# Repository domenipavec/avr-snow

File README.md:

# avr-snow

https://domen.ipavec.net/en/snow-jaslice/

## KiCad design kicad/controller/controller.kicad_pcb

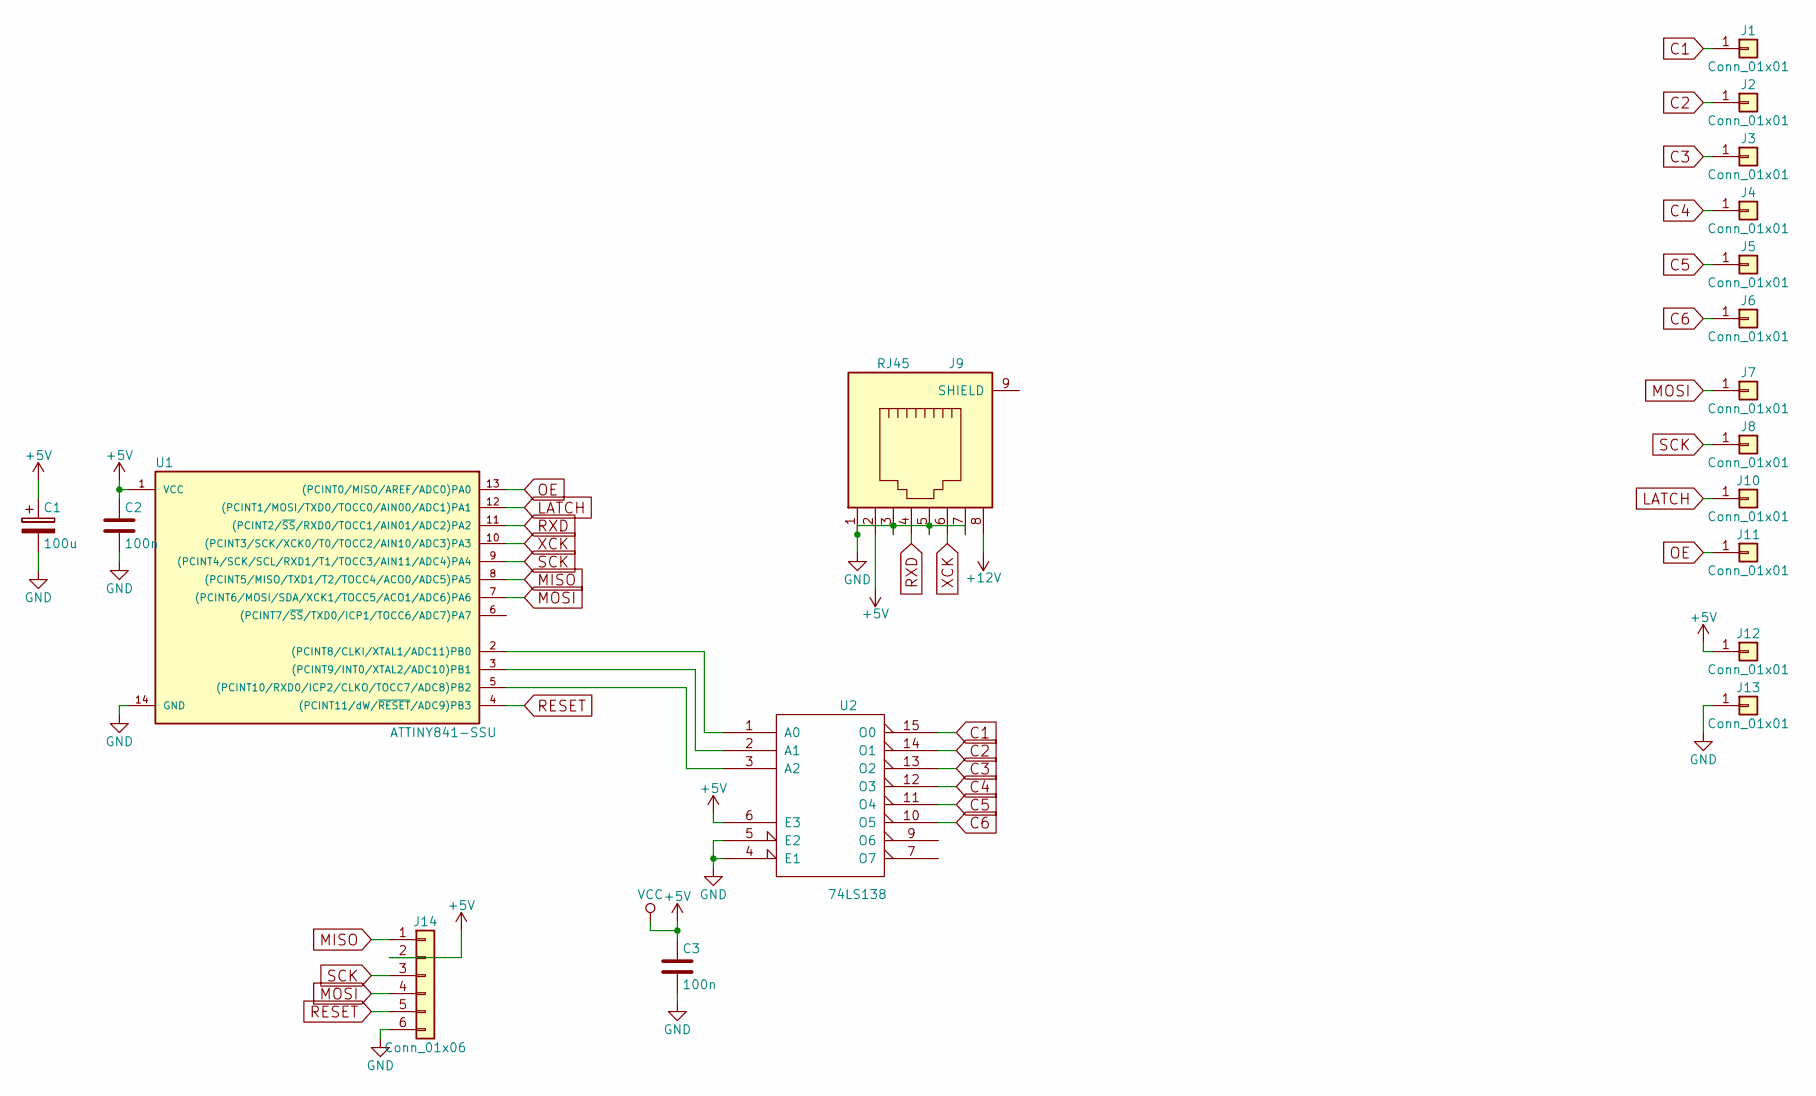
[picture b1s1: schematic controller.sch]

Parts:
C1: 100u; CP_Radial_D6.3mm_P2.50mm
C2, C3: 100n; C_0603_HandSoldering
J1, J2, J3, J4, J5, J6, J7, J8, J10, J11, J12, J13: Conn_01x01; Measurement_Point_Square-SMD-Pad_Big
J9: RJ45
J14: Conn_01x06; Pin_Header_Straight_2x03_Pitch2.54mm
U1: ATTINY841-SSU; SOIC-14_3.9x8.7mm_Pitch1.27mm
U2: 74LS138; SOIC-16W_5.3x10.2mm_Pitch1.27mm

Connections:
+5V: C1.1, C2.1, C3.1, J9.2, J12.1, J14.2, U1.1 (VCC), U2.6 (E3), U2.16 (VCC)
+12V: J9.8
C1: J1.1, U2.15 (O0)
C2: J2.1, U2.14 (O1)
C3: J3.1, U2.13 (O2)
C4: J4.1, U2.12 (O3)
C5: J5.1, U2.11 (O4)
C6: J6.1, U2.10 (O5)
GND: C1.2, C2.2, C3.2, J9.1, J9.3, J9.5, J9.7, J13.1, J14.6, U1.14 (GND), U2.4 (E1), U2.5 (E2), U2.8 (GND)
LATCH: J10.1, U1.12 ((PCINT1/MOSI/TXD0/TOCC0/AIN00/ADC1)PA1)
MISO: J14.1, U1.8 ((PCINT5/MISO/TXD1/T2/TOCC4/ACO0/ADC5)PA5)
MOSI: J7.1, J14.4, U1.7 ((PCINT6/MOSI/SDA/XCK1/TOCC5/ACO1/ADC6)P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)
unnamed: U1.2 ((PCINT8/CLKI/XTAL1/ADC11)PB0), U2.1 (A0)
unnamed: U1.3 ((PCINT9/INT0/XTAL2/ADC10)PB1), U2.2 (A1)
unnamed: U1.5 ((PCINT10/RXD0/ICP2/CLKO/TOCC7/ADC8)PB2), U2.3 (A2)
OE: J11.1, U1.13 ((PCINT0/MISO/AREF/ADC0)PA0)
RESET: J14.5, U1.4 ((PCINT11/dW/~RESET~/ADC9)PB3)
RXD: J9.4, U1.11 ((PCINT2/~SS~/RXD0/TOCC1/AIN01/ADC2)PA2)
SCK: J8.1, J14.3, U1.9 ((PCINT4/SCK/SCL/RXD1/T1/TOCC3/AIN11/ADC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)
XCK: J9.6, U1.10 ((PCINT3/SCK/XCK0/T0/TOCC2/AIN10/ADC3)PA3)

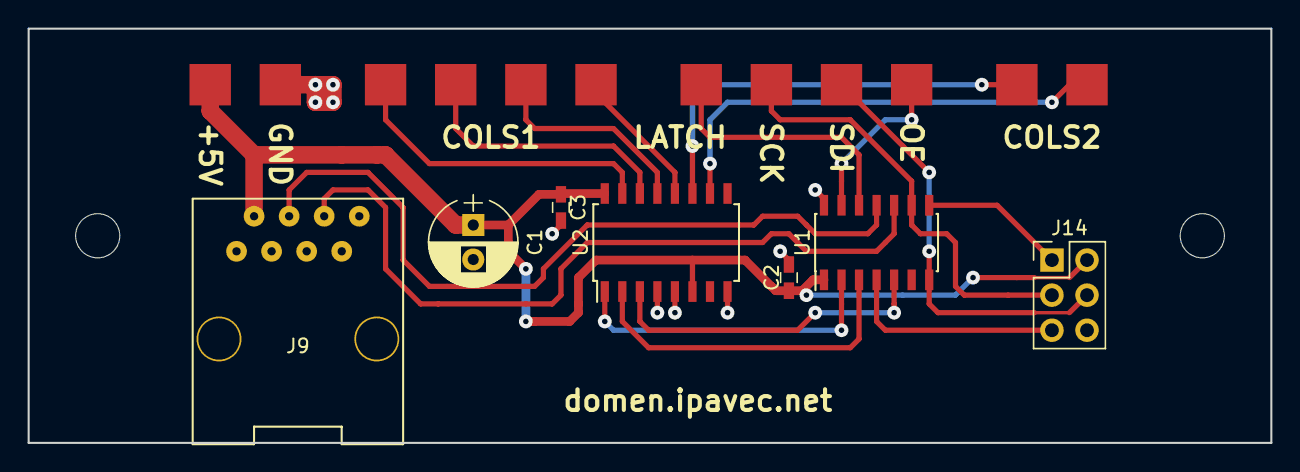
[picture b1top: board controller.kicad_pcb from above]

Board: 2 copper layers, 90.0 x 30.0 mm, 19 parts (0 on the bottom side), 19 nets.

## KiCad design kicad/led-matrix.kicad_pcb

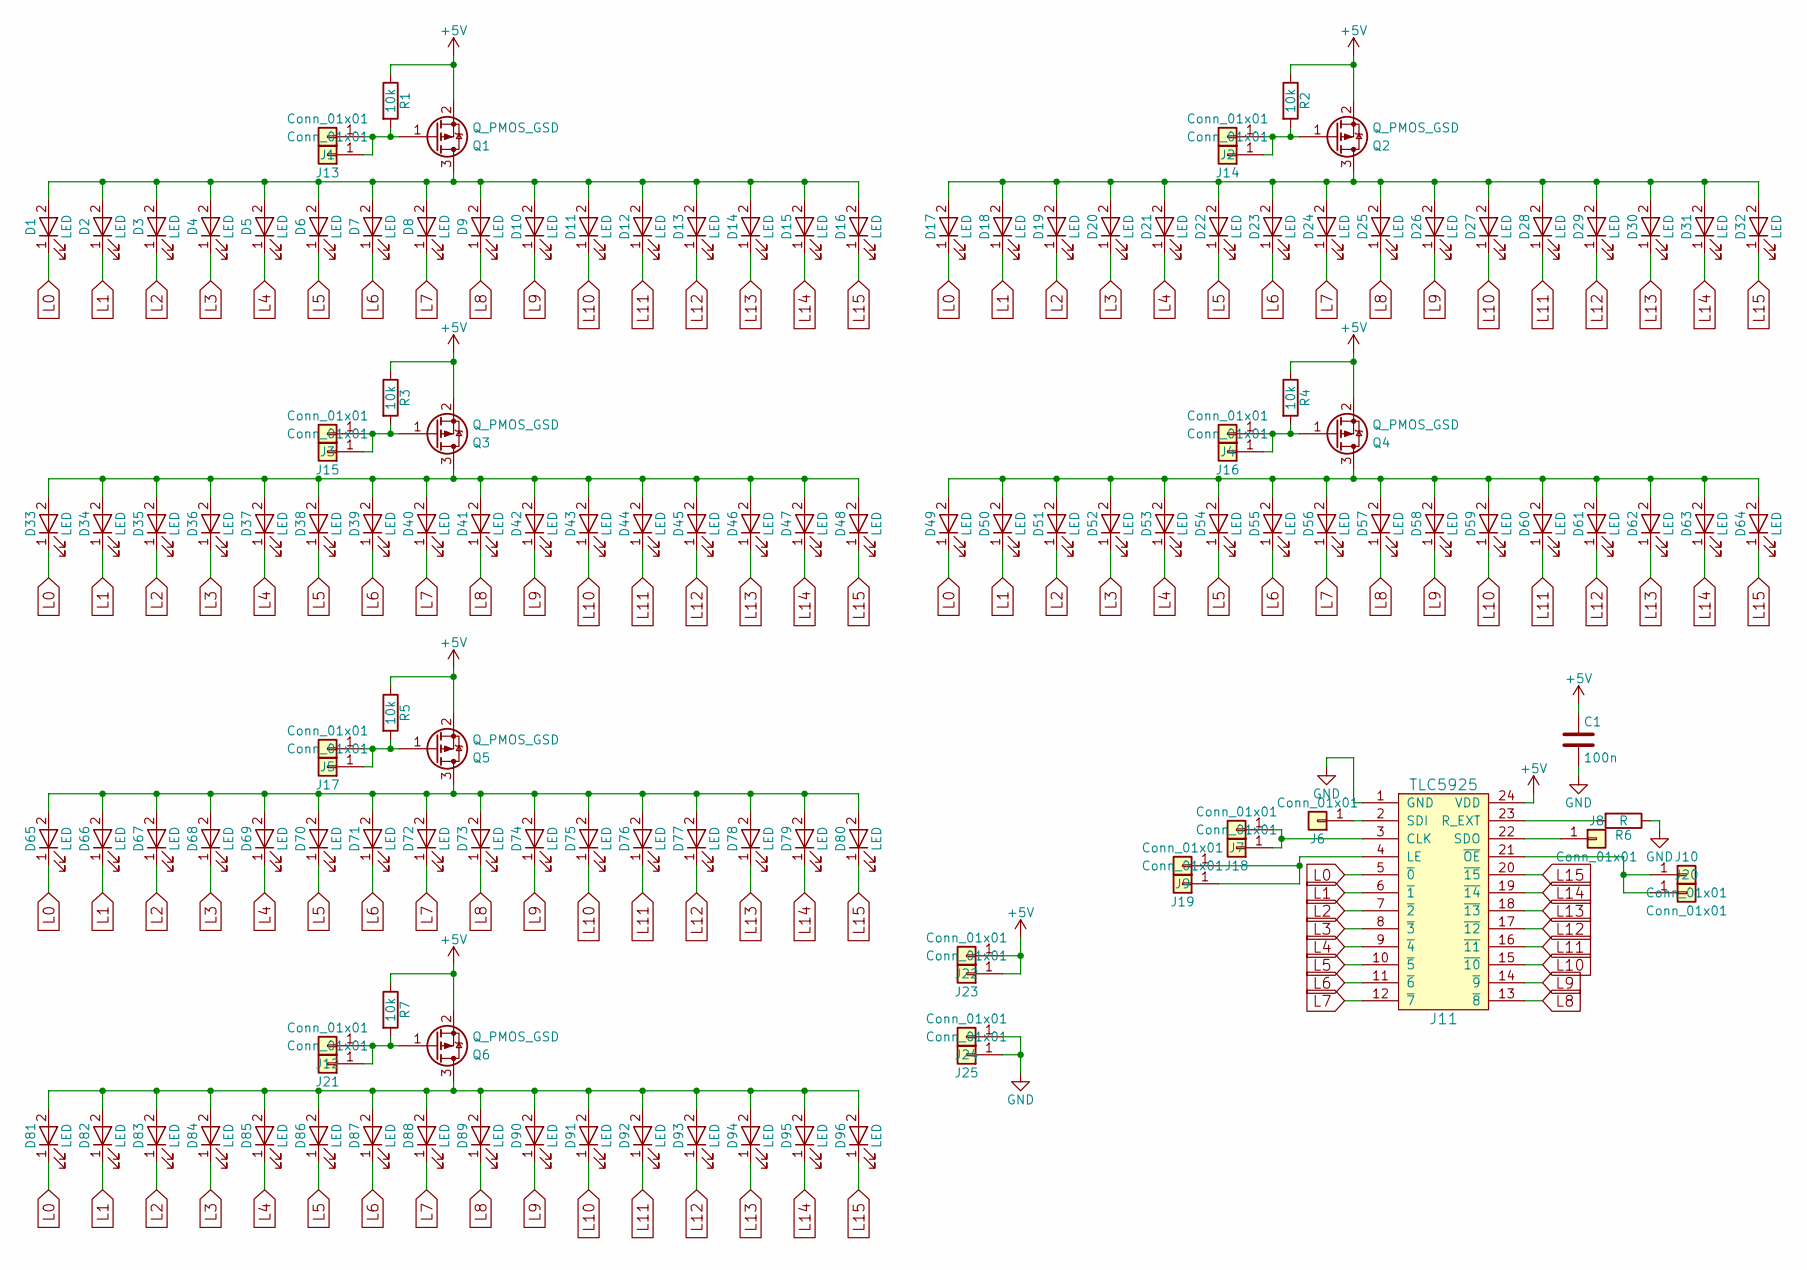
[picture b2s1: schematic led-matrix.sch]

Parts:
C1: 100n; C_0603_HandSoldering
D1, D2, D3, D4, D5, D6, D7, D8, D9, D10, D11, D12, D13, D14, D15, D16, D17, D18, D19, D20, D21, D22, D23, D24, D25, D26, D27, D28, D29, D30, D31, D32, D33, D34, D35, D36, D37, D38, D39, D40, D41, D42, D43, D44, D45, D46, D47, D48, D49, D50, D51, D52, D53, D54, D55, D56, D57, D58, D59, D60, D61, D62, D63, D64, D65, D66, D67, D68, D69, D70, D71, D72, D73, D74, D75, D76, D77, D78, D79, D80, D81, D82, D83, D84, D85, D86, D87, D88, D89, D90, D91, D92, D93, D94, D95, D96: LED; LED_D5.0mm
J1, J2, J3, J4, J5, J6, J7, J8, J9, J10, J12, J13, J14, J15, J16, J17, J18, J19, J20, J21, J22, J23, J24, J25: Conn_01x01; Measurement_Point_Square-SMD-Pad_Big
J11: TLC5925; SOIC-24W_7.5x15.4mm_Pitch1.27mm
Q1, Q2, Q3, Q4, Q5, Q6: Q_PMOS_GSD; SOT-23_Handsoldering
R1, R2, R3, R4, R5, R7: 10k; R_0805_HandSoldering
R6: R; R_0805_HandSoldering

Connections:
+5V: C1.1, J11.24 (VDD), J22.1, J23.1, Q1.2 (S), Q2.2 (S), Q3.2 (S), Q4.2 (S), Q5.2 (S), Q6.2 (S), R1.1, R2.1, R3.1, R4.1, R5.1, R7.1
GND: C1.2, J11.1 (GND), J24.1, J25.1, R6.1
L0: D1.1 (K), D17.1 (K), D33.1 (K), D49.1 (K), D65.1 (K), D81.1 (K), J11.5 (~0)
L1: D2.1 (K), D18.1 (K), D34.1 (K), D50.1 (K), D66.1 (K), D82.1 (K), J11.6 (~1)
L2: D3.1 (K), D19.1 (K), D35.1 (K), D51.1 (K), D67.1 (K), D83.1 (K), J11.7 (~2)
L3: D4.1 (K), D20.1 (K), D36.1 (K), D52.1 (K), D68.1 (K), D84.1 (K), J11.8 (~3)
L4: D5.1 (K), D21.1 (K), D37.1 (K), D53.1 (K), D69.1 (K), D85.1 (K), J11.9 (~4)
L5: D6.1 (K), D22.1 (K), D38.1 (K), D54.1 (K), D70.1 (K), D86.1 (K), J11.10 (~5)
L6: D7.1 (K), D23.1 (K), D39.1 (K), D55.1 (K), D71.1 (K), D87.1 (K), J11.11 (~6)
L7: D8.1 (K), D24.1 (K), D40.1 (K), D56.1 (K), D72.1 (K), D88.1 (K), J11.12 (~7)
L8: D9.1 (K), D25.1 (K), D41.1 (K), D57.1 (K), D73.1 (K), D89.1 (K), J11.13 (~8)
L9: D10.1 (K), D26.1 (K), D42.1 (K), D58.1 (K), D74.1 (K), D90.1 (K), J11.14 (~9)
L10: D11.1 (K), D27.1 (K), D43.1 (K), D59.1 (K), D75.1 (K), D91.1 (K), J11.15 (~10)
L11: D12.1 (K), D28.1 (K), D44.1 (K), D60.1 (K), D76.1 (K), D92.1 (K), J11.16 (~11)
L12: D13.1 (K), D29.1 (K), D45.1 (K), D61.1 (K), D77.1 (K), D93.1 (K), J11.17 (~12)
L13: D14.1 (K), D30.1 (K), D46.1 (K), D62.1 (K), D78.1 (K), D94.1 (K), J11.18 (~13)
L14: D15.1 (K), D31.1 (K), D47.1 (K), D63.1 (K), D79.1 (K), D95.1 (K), J11.19 (~14)
L15: D16.1 (K), D32.1 (K), D48.1 (K), D64.1 (K), D80.1 (K), D96.1 (K), J11.20 (~15)
unnamed: D1.2 (A), D2.2 (A), D3.2 (A), D4.2 (A), D5.2 (A), D6.2 (A), D7.2 (A), D8.2 (A), D9.2 (A), D10.2 (A), D11.2 (A), D12.2 (A), D13.2 (A), D14.2 (A), D15.2 (A), D16.2 (A), Q1.3 (D)
unnamed: D17.2 (A), D18.2 (A), D19.2 (A), D20.2 (A), D21.2 (A), D22.2 (A), D23.2 (A), D24.2 (A), D25.2 (A), D26.2 (A), D27.2 (A), D28.2 (A), D29.2 (A), D30.2 (A), D31.2 (A), D32.2 (A), Q2.3 (D)
unnamed: D33.2 (A), D34.2 (A), D35.2 (A), D36.2 (A), D37.2 (A), D38.2 (A), D39.2 (A), D40.2 (A), D41.2 (A), D42.2 (A), D43.2 (A), D44.2 (A), D45.2 (A), D46.2 (A), D47.2 (A), D48.2 (A), Q3.3 (D)
unnamed: D49.2 (A), D50.2 (A), D51.2 (A), D52.2 (A), D53.2 (A), D54.2 (A), D55.2 (A), D56.2 (A), D57.2 (A), D58.2 (A), D59.2 (A), D60.2 (A), D61.2 (A), D62.2 (A), D63.2 (A), D64.2 (A), Q4.3 (D)
unnamed: D65.2 (A), D66.2 (A), D67.2 (A), D68.2 (A), D69.2 (A), D70.2 (A), D71.2 (A), D72.2 (A), D73.2 (A), D74.2 (A), D75.2 (A), D76.2 (A), D77.2 (A), D78.2 (A), D79.2 (A), D80.2 (A), Q5.3 (D)
unnamed: D81.2 (A), D82.2 (A), D83.2 (A), D84.2 (A), D85.2 (A), D86.2 (A), D87.2 (A), D88.2 (A), D89.2 (A), D90.2 (A), D91.2 (A), D92.2 (A), D93.2 (A), D94.2 (A), D95.2 (A), D96.2 (A), Q6.3 (D)
unnamed: J1.1, J13.1, Q1.1 (G), R1.2
unnamed: J10.1, J11.21 (~OE), J20.1
unnamed: J6.1, J11.2 (SDI)
unnamed: J7.1, J11.3 (CLK), J18.1
unnamed: J9.1, J11.4 (LE), J19.1
unnamed: J8.1, J11.22 (SDO)
unnamed: J11.23 (R_EXT), R6.2
unnamed: J12.1, J21.1, Q6.1 (G), R7.2
unnamed: J2.1, J14.1, Q2.1 (G), R2.2
unnamed: J3.1, J15.1, Q3.1 (G), R3.2
unnamed: J4.1, J16.1, Q4.1 (G), R4.2
unnamed: J5.1, J17.1, Q5.1 (G), R5.2

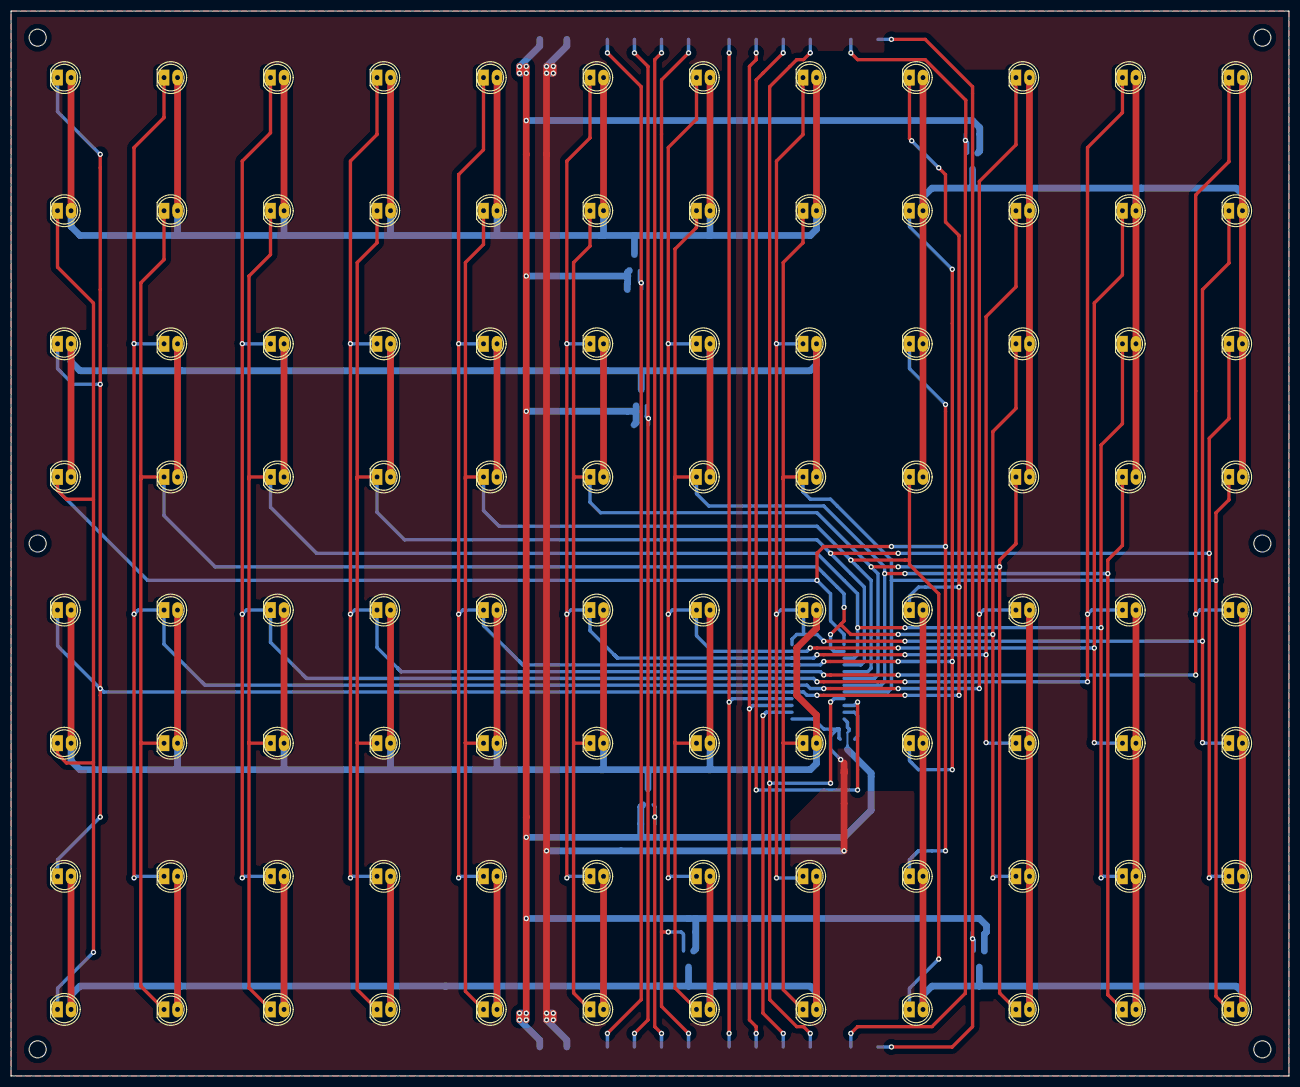
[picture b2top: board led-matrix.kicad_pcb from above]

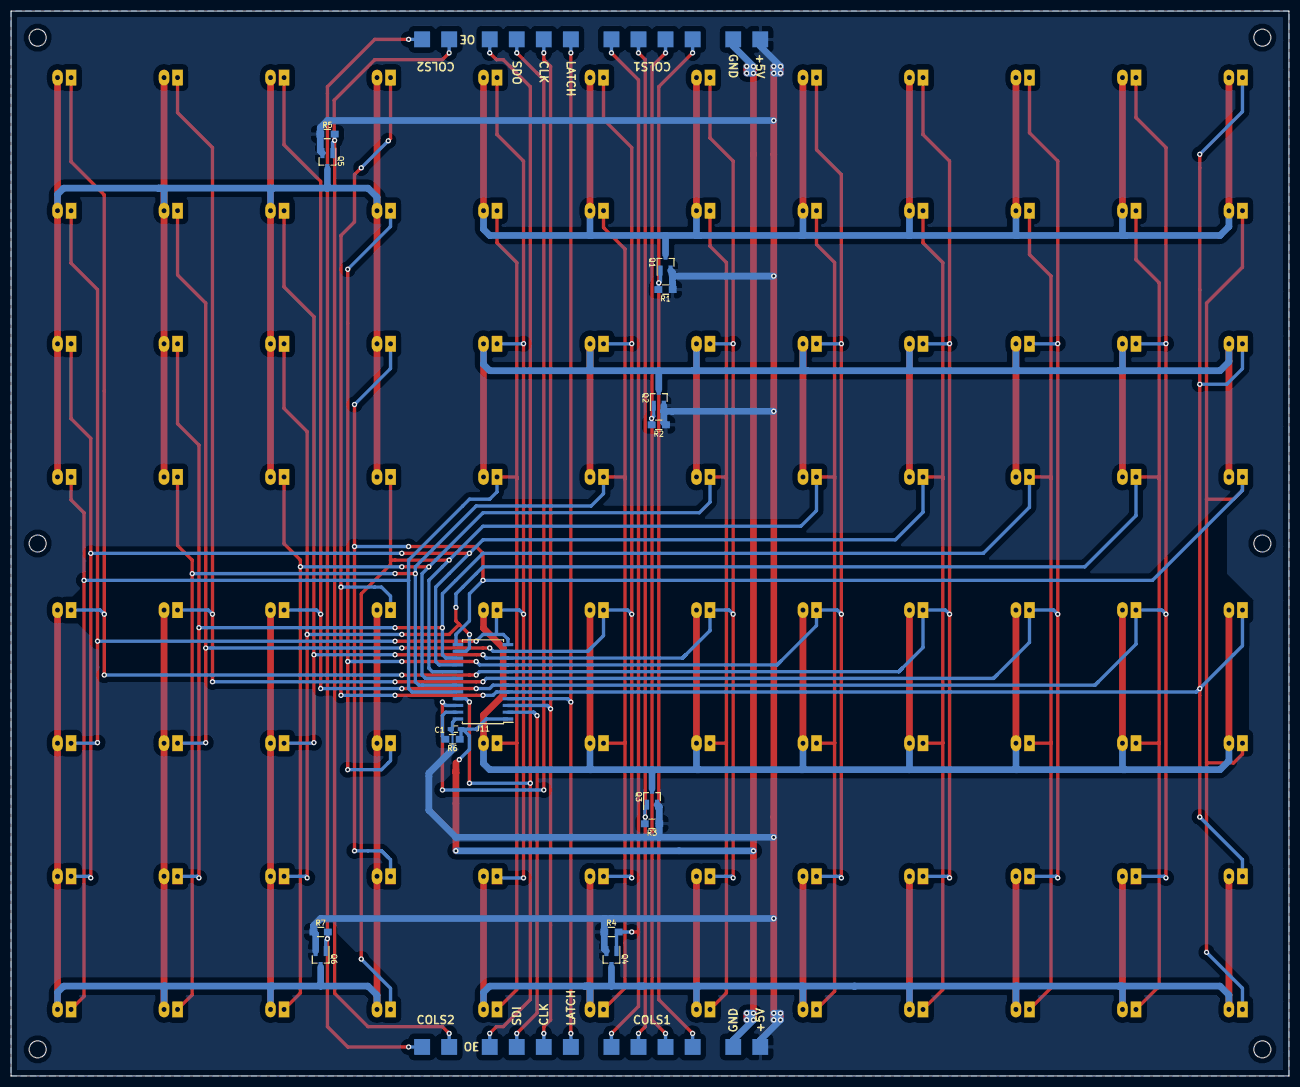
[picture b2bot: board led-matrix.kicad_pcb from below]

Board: 2 copper layers, 240.0 x 200.0 mm, 135 parts (39 on the bottom side), 36 nets.

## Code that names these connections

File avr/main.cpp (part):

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			TCNT0 = 0;

			// disable output
			SETBIT(PORTA, PA0);

			// go to new column selector
			spi_state = 0;
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			}

			// latch new data
			SETBIT(PORTA, PA1);
			CLEARBIT(PORTA, PA1);

			// enable output
			CLEARBIT(PORTA, PA0);
			spi_send();
		}
	}
	if (TCNT0 >= pwm) {
		SETBIT(PORTA, PA0);
	}
}

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	// init

	// output enable always on
	SETBIT(DDRA, PA0);
	CLEARBIT(PORTA, PA0);

	// latch init
	SETBIT(DDRA, PA1);
	CLEARBIT(PORTA, PA1);

	// column control pins as output
	SETBITS(DDRB, BIT(PB0) | BIT(PB1) | BIT(PB2));

	// spi init
	// mosi, sck, ss!(this is needed for spi to work)! as outputs
	SETBITS(DDRA, BIT(PA6)|BIT(PA4)|BIT(PA7));
	// spi enable, interrupt enable, master, fastest clock
	SPCR = BIT(SPE) | BIT(MSTR);
	// double speed (fclk/2)
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
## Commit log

2017-10-16 Snow simulation
2017-10-16 Added stars mode
2017-10-26 Added kicad led-matrix pcb
2017-10-26 Updated board size
2017-10-29 Move led matrix to separate folder
2017-11-01 Better color definition
2017-11-01 Constelation based on last year
2017-11-03 Added controller pcb
2017-11-13 Move snow to simulation
2017-11-22 Working transition without pwm
2017-11-22 Working pwm
2017-12-02 Real coordinates
2017-12-02 All stars in simulation
2017-12-06 uart control + final code
2017-12-08 Added remote code
2018-01-02 Add LICENCE

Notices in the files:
avr/main.cpp:
Copyright (c) 2017 Domen Ipavec (domen@ipavec.net)
